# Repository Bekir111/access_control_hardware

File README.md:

# Access Control Hardware 

This repository contains the KiCad schematics and PCB designs for the Access Control System.

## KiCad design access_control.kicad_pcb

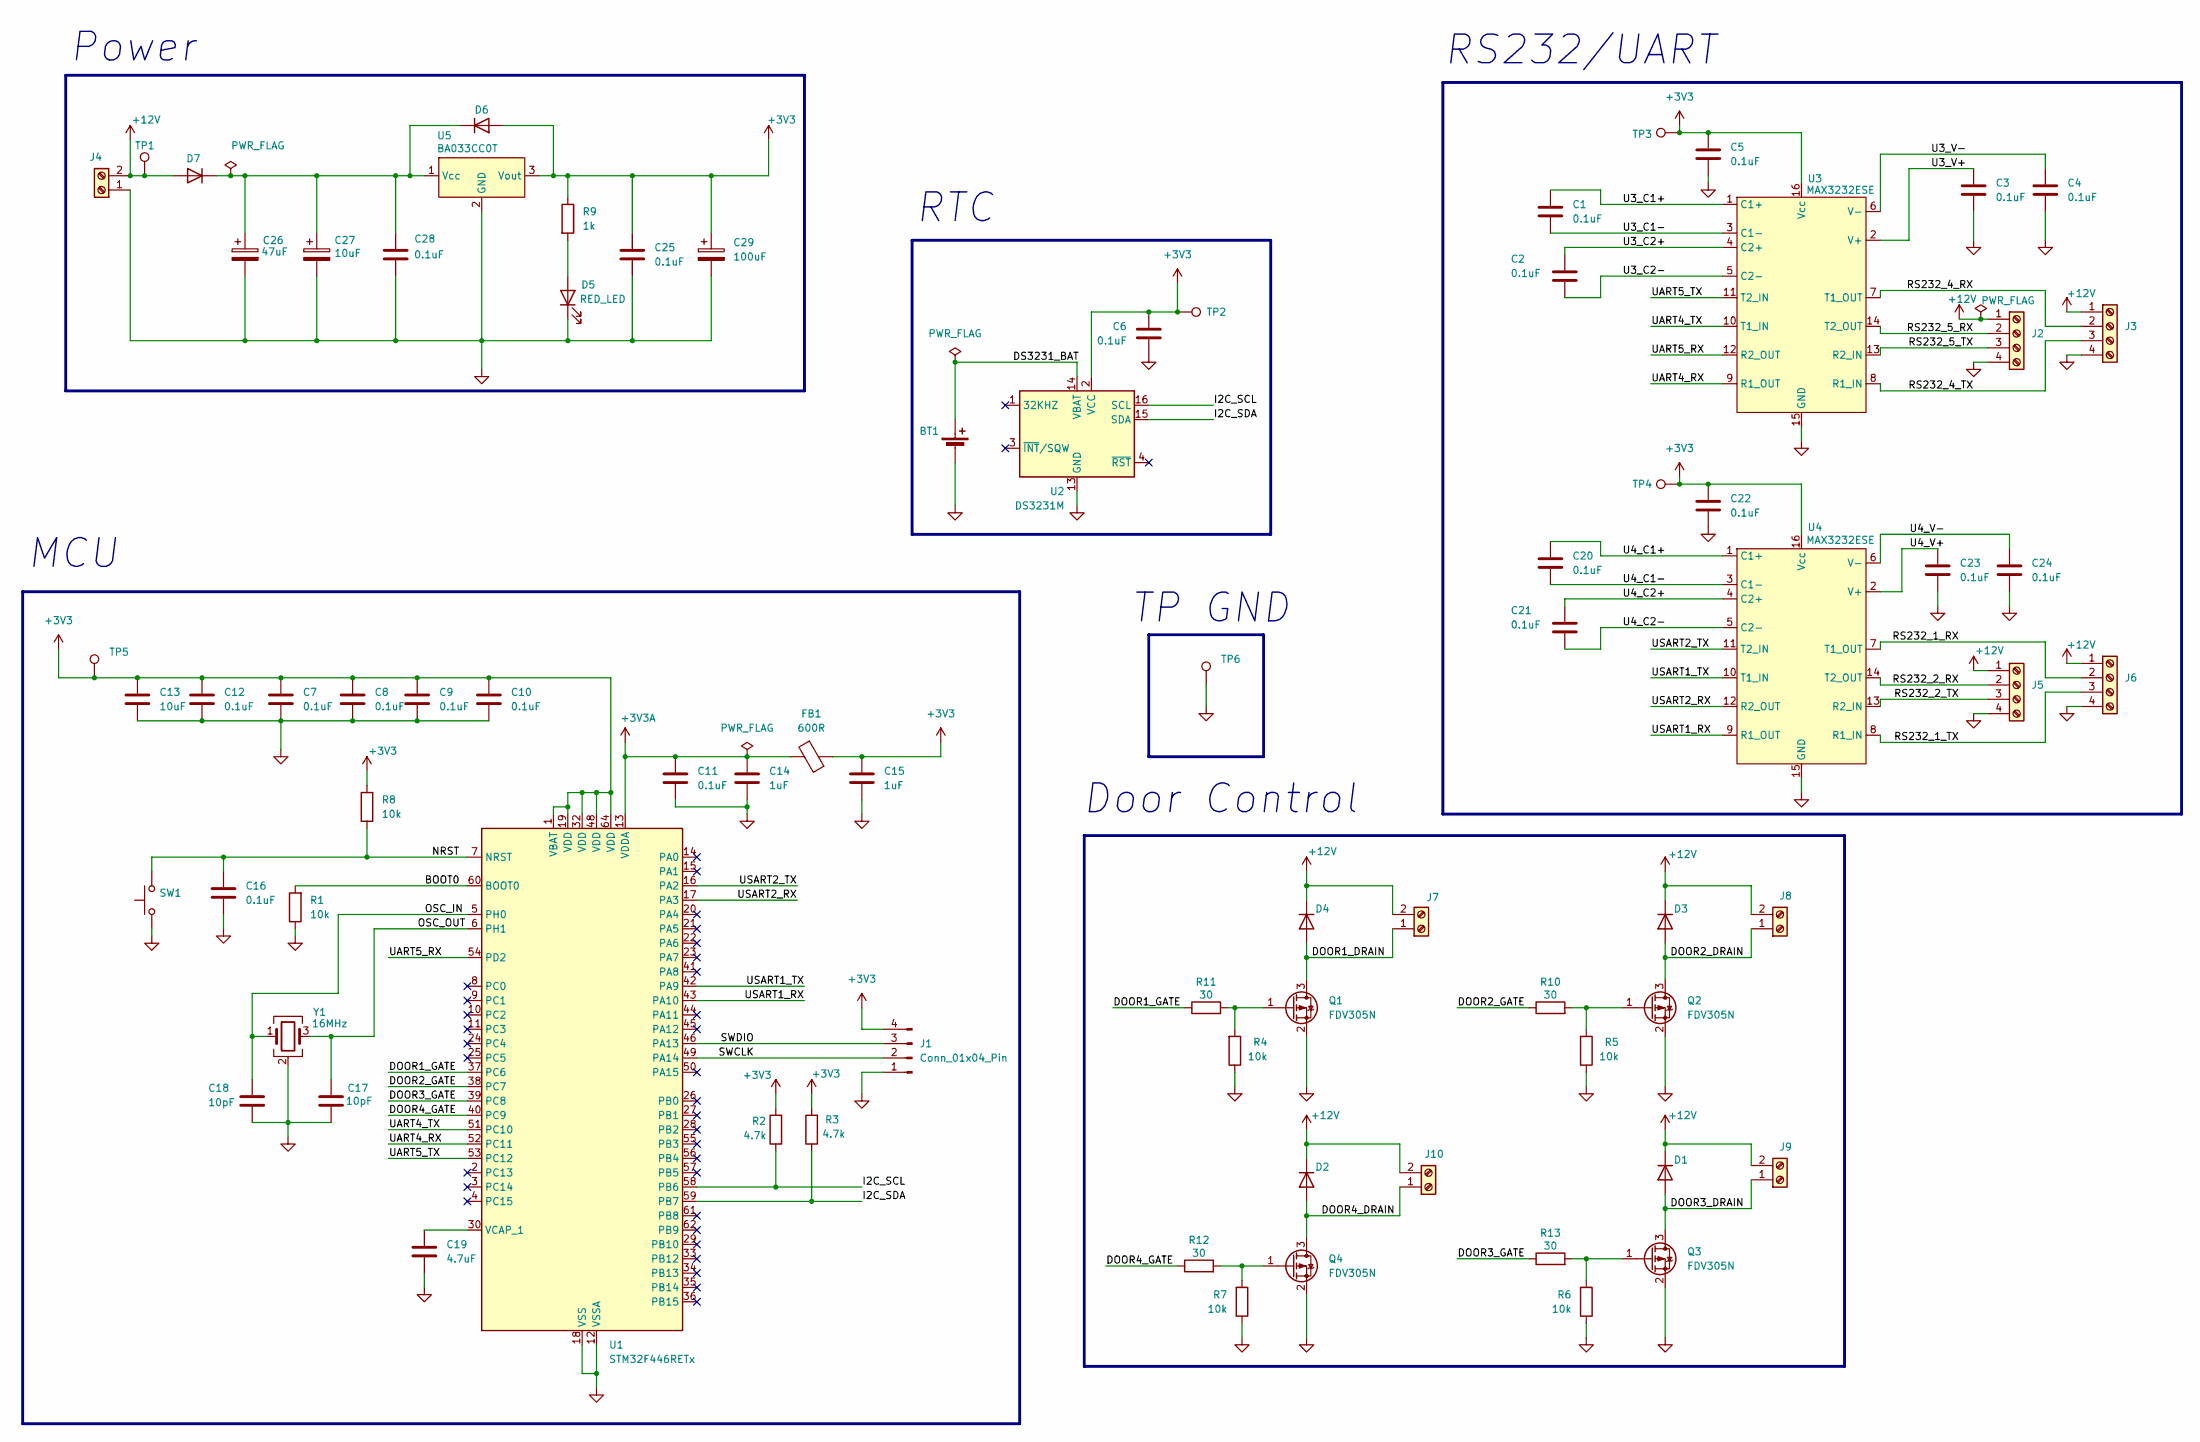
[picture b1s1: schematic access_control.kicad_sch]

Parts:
BT1: Battery_Cell; BatteryHolder_Keystone_1060_1x2032; LCSC C70377
C1, C2, C3, C4, C5, C6, C7, C8, C9, C10, C11, C12, C16, C20, C21, C22, C23, C24, C25, C28: 0.1uF; C_0805_2012Metric_Pad1.18x1.45mm_HandSolder; LCSC C1711
C13: 10uF; C_0805_2012Metric_Pad1.18x1.45mm_HandSolder; LCSC C15850
C14, C15: 1uF; C_0805_2012Metric_Pad1.18x1.45mm_HandSolder; LCSC C91185
C17, C18: 10pF; C_0805_2012Metric_Pad1.18x1.45mm_HandSolder; MPN CC0805JRNPO9BN100; LCSC C107107
C19: 4.7uF; C_0805_2012Metric_Pad1.18x1.45mm_HandSolder; MPN CL21A475KAQNNNE
C26: 47uF; CP_Radial_D6.3mm_P2.50mm; MPN EXR470M35B
C27: 10uF; CP_Radial_D5.0mm_P2.50mm; MPN RK1V100M-TSD11
C29: 100uF; CP_Radial_D6.3mm_P2.50mm; MPN RM1C101M-RBE07
D1, D2, D3, D4, D6, D7: D; D_SMA-SMB_Universal_Handsoldering; MPN M7; LCSC C2972759
D5: RED_LED; LED_D3.0mm
FB1: 600R; L_0805_2012Metric_Pad1.05x1.20mm_HandSolder; MPN BLM21BD601SN1D; LCSC C341663
J1: Conn_01x04_Pin; PinHeader_1x04_P2.54mm_Vertical
J2, J3, J5, J6: Screw_Terminal_01x04; TerminalBlock_Phoenix_MKDS-1,5-4-5.08_1x04_P5.08mm_Horizont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
J4, J7, J8, J9, J10: Screw_Terminal_01x02; TerminalBlock_Phoenix_MKDS-1,5-2-5.08_1x02_P5.08mm_Horizont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
Q1, Q2, Q3, Q4: FDV305N; SOT-23; MPN FDV305N; LCSC C154511
R1, R4, R5, R6, R7, R8: 10k; R_0805_2012Metric_Pad1.20x1.40mm_HandSolder; MPN RC0805FR-0710KL; LCSC C84376
R2, R3: 4.7k; R_0805_2012Metric_Pad1.20x1.40mm_HandSolder; MPN CRCW08054K70JNTABC; LCSC C2907326
R9: 1k; R_0805_2012Metric_Pad1.20x1.40mm_HandSolder; MPN RC0805FR-071KL; LCSC C2907295
R10, R11, R12, R13: 30; R_0805_2012Metric_Pad1.20x1.40mm_HandSolder; MPN CRCW080530R0FKTABC; LCSC C2907256
SW1: Reset button; SW_SPST_PTS645Sx43SMTR92; MPN TS110416043; LCSC C22375342
TP1, TP2, TP3, TP4, TP5, TP6: TestPoint; TestPoint_Pad_D2.0mm
U1: STM32F446RETx; LQFP-64_10x10mm_P0.5mm; MPN STM32F446RET6; LCSC C69336
U2: DS3231M; SOIC-16W_7.5x10.3mm_P1.27mm; MPN DS3231SN#T&R; LCSC C9866
U3, U4: MAX3232ESE; SOIC-16_3.9x9.9mm_P1.27mm; LCSC C143435
U5: BA033CC0T; TO-220-3_Horizontal_TabDown; MPN BA033CC0T; LCSC C184572
Y1: 16MHz; Crystal_SMD_3225-4Pin_3.2x2.5mm_HandSoldering; MPN X322516MKB4SI; LCSC C13738

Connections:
+3V3: C5.1, C6.1, C7.1, C8.1, C9.1, C10.1, C12.1, C13.1, C15.1, C22.1, C25.1, C29.1, D6.2 (A), FB1.2, J1.4, R2.2, R3.2, R8.2, R9.1, TP2.1, TP3.1, TP4.1, TP5.1, U1.1 (VBAT), U1.19 (VDD), U1.32 (VDD), U1.48 (VDD), U1.64 (VDD), U2.2 (VCC), U3.16 (Vcc), U4.16 (Vcc), U5.3 (Vout)
+3V3A: C11.1, C14.1, FB1.1, U1.13 (VDDA)
+12V: D1.1 (K), D2.1 (K), D3.1 (K), D4.1 (K), D7.2 (A), J2.1, J3.1, J4.2, J5.1, J6.1, J7.2, J8.2, J9.2, J10.2, TP1.1
/BOOT0: R1.2, U1.60 (BOOT0)
/DOOR1_DRAIN: D4.2 (A), J7.1, Q1.3 (D)
/DOOR1_GATE: R11.1, U1.37 (PC6)
/DOOR2_DRAIN: D3.2 (A), J8.1, Q2.3 (D)
/DOOR2_GATE: R10.1, U1.38 (PC7)
/DOOR3_DRAIN: D1.2 (A), J9.1, Q3.3 (D)
/DOOR3_GATE: R13.1, U1.39 (PC8)
/DOOR4_DRAIN: D2.2 (A), J10.1, Q4.3 (D)
/DOOR4_GATE: R12.1, U1.40 (PC9)
/DS3231_BAT: BT1.1 (+), U2.14 (VBAT)
/I2C_SCL: R2.1, U1.58 (PB6), U2.16 (SCL)
/I2C_SDA: R3.1, U1.59 (PB7), U2.15 (SDA)
/NRST: C16.1, R8.1, SW1.2, U1.7 (NRST)
/OSC_IN: C18.1, U1.5 (PH0), Y1.1
/OSC_OUT: C17.1, U1.6 (PH1), Y1.3
/RS232_1_RX: J6.2, U4.7 (T1_OUT)
/RS232_1_TX: J6.3, U4.8 (R1_IN)
/RS232_2_RX: J5.2, U4.14 (T2_OUT)
/RS232_2_TX: J5.3, U4.13 (R2_IN)
/RS232_4_RX: J3.2, U3.7 (T1_OUT)
/RS232_4_TX: J3.3, U3.8 (R1_IN)
/RS232_5_RX: J2.2, U3.14 (T2_OUT)
/RS232_5_TX: J2.3, U3.13 (R2_IN)
/SWCLK: J1.2, U1.49 (PA14)
/SWDIO: J1.3, U1.46 (PA13)
/U3_C1+: C1.1, U3.1 (C1+)
/U3_C1-: C1.2, U3.3 (C1-)
/U3_C2+: C2.1, U3.4 (C2+)
/U3_C2-: C2.2, U3.5 (C2-)
/U3_V+: C3.1, U3.2 (V+)
/U3_V-: C4.1, U3.6 (V-)
/U4_C1+: C20.1, U4.1 (C1+)
/U4_C1-: C20.2, U4.3 (C1-)
/U4_C2+: C21.1, U4.4 (C2+)
/U4_C2-: C21.2, U4.5 (C2-)
/U4_V+: C23.1, U4.2 (V+)
/U4_V-: C24.1, U4.6 (V-)
/UART4_RX: U1.52 (PC11), U3.9 (R1_OUT)
/UART4_TX: U1.51 (PC10), U3.10 (T1_IN)
/UART5_RX: U1.54 (PD2), U3.12 (R2_OUT)
/UART5_TX: U1.53 (PC12), U3.11 (T2_IN)
/USART1_RX: U1.43 (PA10), U4.9 (R1_OUT)
/USART1_TX: U1.42 (PA9), U4.10 (T1_IN)
/USART2_RX: U1.17 (PA3), U4.12 (R2_OUT)
/USART2_TX: U1.16 (PA2), U4.11 (T2_IN)
GND: BT1.2 (-), C3.2, C4.2, C5.2, C6.2, C7.2, C8.2, C9.2, C10.2, C11.2, C12.2, C13.2, C14.2, C15.2, C16.2, C17.2, C18.2, C19.2, C22.2, C23.2, C24.2, C25.2, C26.2, C27.2, C28.2, C29.2, D5.1 (K), J1.1, J2.4, J3.4, J4.1, J5.4, J6.4, Q1.2 (S), Q2.2 (S), Q3.2 (S), Q4.2 (S), R1.1, R4.1, R5.1, R6.1, R7.1, SW1.1, TP6.1, U1.12 (VSSA), U1.18 (VSS), U1.31 (VSS), U1.47 (VSS), U1.63 (VSS), U2.5 (GND), U2.6 (GND), U2.7 (GND), U2.8 (GND), U2.9 (GND), U2.10 (GND), U2.11 (GND), U2.12 (GND), U2.13 (GND), U3.15 (GND), U4.15 (GND), U5.2 (GND), Y1.2 (G), Y1.4 (G)
unnamed: D5.2 (A), R9.2
unnamed: C26.1, C27.1, C28.1, D6.1 (K), D7.1 (K), U5.1 (Vcc)
unnamed: Q1.1 (G), R4.2, R11.2
unnamed: Q2.1 (G), R5.2, R10.2
unnamed: Q3.1 (G), R6.2, R13.2
unnamed: Q4.1 (G), R7.2, R12.2
unnamed: C19.1, U1.30 (VCAP_1)

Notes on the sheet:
Door Control
TP GND
RS232/UART
MCU
RTC
Power

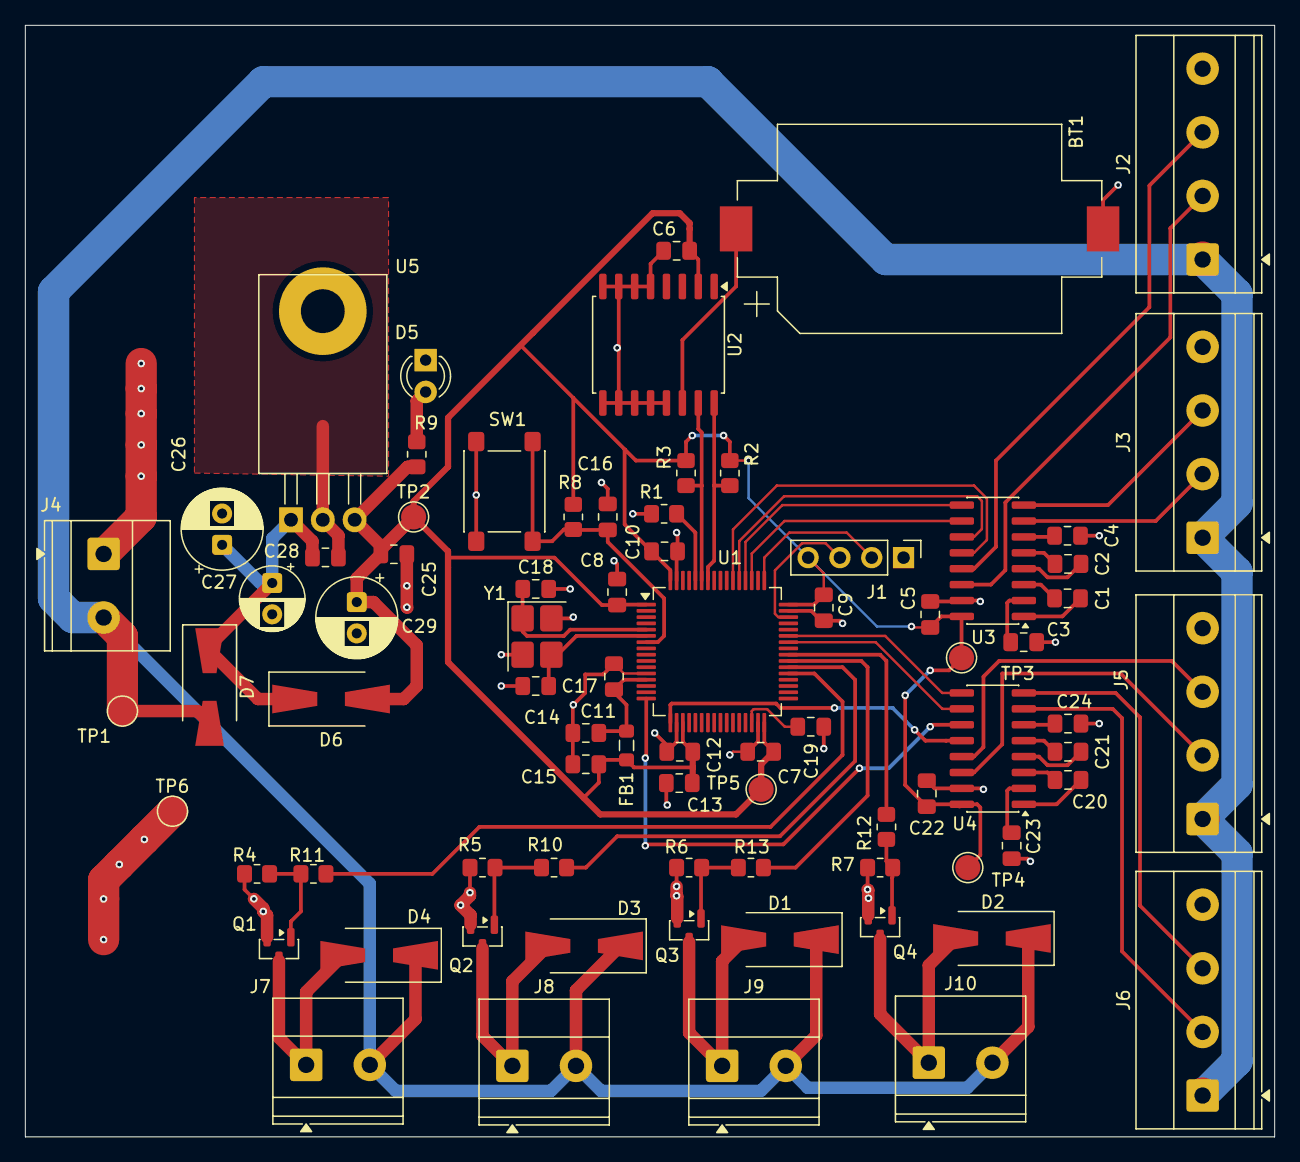
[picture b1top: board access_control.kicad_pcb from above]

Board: 2 copper layers, 99.8 x 88.8 mm, 78 parts (0 on the bottom side), 56 nets.

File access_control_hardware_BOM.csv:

"Reference","Qty","Value","DNP","Exclude from BOM","Exclude from Board","Footprint","Datasheet","MPN","Manufacturer","Manufacturer Part Number","`Manufactuer Part Number"
"BT1","1","Battery_Cell","","","","Battery:BatteryHolder_Keystone_1060_1x2032","~","","","",""
"C1,C2,C3,C4,C5,C6,C7,C8,C9,C10,C11,C12,C16,C20,C21,C22,C23,C24,C25,C28","20","0.1uF","","","","Capacitor_SMD:C_0805_2012Metric_Pad1.18x1.45mm_HandSolder","~","","Samsung Electro-Mechanics","","CL21B104KBCNNNC"
"C13","1","10uF","","","","Capacitor_SMD:C_0805_2012Metric_Pad1.18x1.45mm_HandSolder","~","","Samsung Electro-Mechanics","","CL21A106KAYNNNE"
"C14,C15","2","1uF","","","","Capacitor_SMD:C_0805_2012Metric_Pad1.18x1.45mm_HandSolder","~","","YAGEO","","CC0805KKX7R9BB105"
"C17,C18","2","10pF","","","","Capacitor_SMD:C_0805_2012Metric_Pad1.18x1.45mm_HandSolder","~","CC0805JRNPO9BN100","YAGEO","",""
"C19","1","4.7uF","","","","Capacitor_SMD:C_0805_2012Metric_Pad1.18x1.45mm_HandSolder","~","CL21A475KAQNNNE","SAMSUNG ELECTRO-MECHANICS","",""
"C26","1","47uF","","","","Capacitor_THT:CP_Radial_D6.3mm_P2.50mm","~","EXR470M35B","HITANO ENTERPRISE CORP. ","",""
"C27","1","10uF","","","","Capacitor_THT:CP_Radial_D5.0mm_P2.50mm","~","RK1V100M-TSD11","FUJICON","",""
"C29","1","100uF","","","","Capacitor_THT:CP_Radial_D6.3mm_P2.50mm","~","RM1C101M-RBE07","FUJICON","",""
"D1,D2,D3,D4,D6,D7","6","D","","","","Diode_SMD:D_SMA-SMB_Universal_Handsoldering","~","M7","Tong Ke / Diotec Semiconductor","",""
"D5","1","RED_LED","","","","LED_THT:LED_D3.0mm","~","","","",""
"FB1","1","600R","","","","Inductor_SMD:L_0805_2012Metric_Pad1.05x1.20mm_HandSolder","~","BLM21BD601SN1D","Murata Electronics","",""
"J1","1","Conn_01x04_Pin","","","","Connector_PinHeader_2.54mm:PinHeader_1x04_P2.54mm_Vertical","~","","","",""
"J2,J3,J5,J6","4","Screw_Terminal_01x04","","","","TerminalBlock_Phoenix:TerminalBlock_Phoenix_MKDS-1,5-4-5.08_1x04_P5.08mm_Horizontal","~","","","",""
"J4,J7,J8,J9,J10","5","Screw_Terminal_01x02","","","","TerminalBlock_Phoenix:TerminalBlock_Phoenix_MKDS-1,5-2-5.08_1x02_P5.08mm_Horizontal","~","","","",""
"Q1,Q2,Q3,Q4","4","NMOS","","","","Package_TO_SOT_SMD:SOT-23_Handsoldering","https://store.comet.bg/download-file.php?id=24383","FDV305N","onsemi","",""
"R1,R4,R5,R6,R7,R8","6","10k","","","","Resistor_SMD:R_0805_2012Metric_Pad1.20x1.40mm_HandSolder","~","RC0805FR-0710KL","YAGEO","",""
"R2,R3","2","4.7k","","","","Resistor_SMD:R_0805_2012Metric_Pad1.20x1.40mm_HandSolder","~","CRCW08054K70JNTABC","VISHAY","",""
"R9","1","1k","","","","Resistor_SMD:R_0805_2012Metric_Pad1.20x1.40mm_HandSolder","~","RC0805FR-071KL","YAGEO","",""
"R10,R11,R12,R13","4","30","","","","Resistor_SMD:R_0805_2012Metric_Pad1.20x1.40mm_HandSolder","~","CRCW080530R0FKTABC","VISHAY ","",""
"SW1","1","Reset button","","","","Button_Switch_SMD:SW_SPST_PTS645Sx43SMTR92","~","TS110416043","HanElectricity","",""
"TP1,TP2,TP3,TP4,TP5,TP6","6","TestPoint","","","","TestPoint:TestPoint_Pad_D2.0mm","~","","","",""
"U1","1","STM32F446RETx","","","","Package_QFP:LQFP-64_10x10mm_P0.5mm","https://www.st.com/resource/en/datasheet/stm32f446re.pdf","STM32F446RET6","ST","",""
"U2","1","DS3231M","","","","Package_SO:SOIC-16W_7.5x10.3mm_P1.27mm","http://datasheets.maximintegrated.com/en/ds/DS3231.pdf","DS3231SN#T&R","MAXIM","",""
"U3,U4","2","MAX3232ESE","","","","Package_SO:SOIC-16_3.9x9.9mm_P1.27mm","https://eu.mouser.com/datasheet/3/1014/1/MAX3222-MAX3241.pdf","","Analog Devices Inc.","",""
"U5","1","BA033CC0T","","","","Package_TO_SOT_THT:TO-220-3_Horizontal_TabDown","https://store.comet.bg/download-file.php?id=4908","BA033CC0T","ROHM","",""
"Y1","1","16MHz","","","","Crystal:Crystal_SMD_3225-4Pin_3.2x2.5mm_HandSoldering","","X322516MKB4SI","YANGXING TECHNOLOGY Co., Ltd","",""

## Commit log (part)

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2026-05-07 Inital commit for hardware part of the Access Control diploma project
2026-05-07 Added backups and local setting to gitignore file
2026-05-07 Untracked backup folder and local settings
2026-05-15 Created schematic symbol for MAX3232ESE+ chip
2026-05-19 Drew the typical operating system for MAX3232 chip
2026-05-22 Drwe typical operating circuit for ds3231 and started with MCU's circuit
2026-05-24 Added decoupling capacitors for Vdd and Vdda. Drew HSE oscillator. BOOT0 connected to ground via 10k pull-down. Boot connected to ground via capacitor and swith for manual reset option.
2026-05-24 Added SWD connectors. Added 4.7u capacitor to VCAP_1. Changed all SMD footprints to HandSolder
2026-05-26 Connected DS3231 and MAX3232 to the MCU
2026-06-01 Created new symbol for the voltage regulator
2026-06-01 Connected the MOSFETS to the door control pins. Added footprints and info about the mosfets that i will use. Same information added for the voltage regulator
2026-06-01 Placed the needed capacitors around the BA033CC0T
2026-06-02 Added pull up resistor 10k to the NRST pin
2026-06-02 ERC check verified
2026-06-02 Assigned footprint and information about the diodes D1-4. Added functional block frames.
2026-06-03 Added LED indication for 3.3V
2026-06-04 Changed the oscillator with another one that is in stock
2026-06-04 Placed 30 Ohms resistors to every transistors gate
2026-06-04 Chnged the VCAP capacitor with another that is in stock
2026-06-11 Created BOM for the project
2026-06-11 Component placement for the PCB is ready.
2026-06-14 Finished the PCB routing and placement of the components.
2026-06-17 Finilized editing PCB, generated BOM and grb files. PCB files are sent to JLCPCB
